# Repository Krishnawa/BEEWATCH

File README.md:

## Cloning the Repository and Updating Submodules  

To properly set up this project, follow these steps:  

### 1. Clone the Repository  
Use the `--recurse-submodules` flag to clone the repository along with its submodules:  

```sh
git clone --recurse-submodules https://github.com/Krishnawa/BEEWATCH.git
```
If you have already cloned the repository without submodules, initialize and update them manually:
```sh
git submodule update --init --recursive --remote
```

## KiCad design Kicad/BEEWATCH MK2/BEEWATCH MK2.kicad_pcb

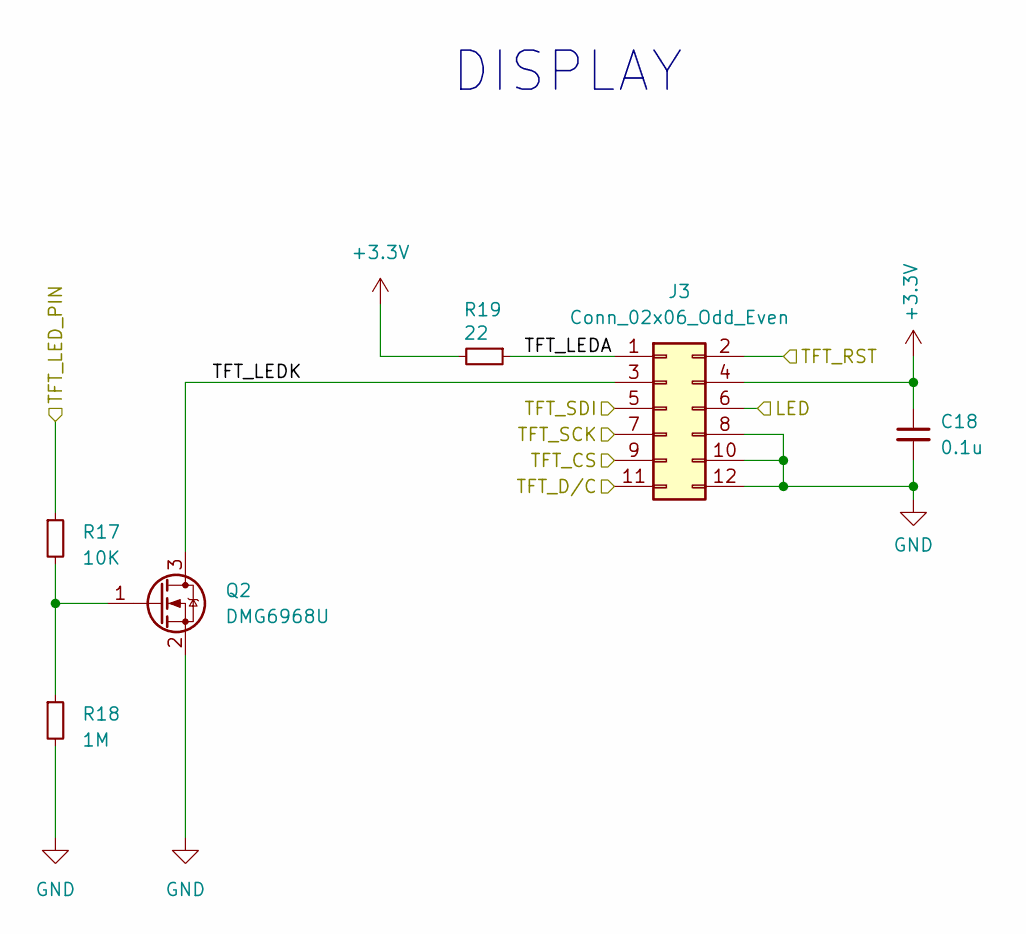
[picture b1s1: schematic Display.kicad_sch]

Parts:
C18: 0.1u; C_0603_1608Metric
J3: Conn_02x06_Odd_Even; PinHeader_2x06_P1.27mm_Vertical_SMD
Q2: DMG6968U; SOT-23
R17: 10K; R_0402_1005Metric_Pad0.72x0.64mm_HandSolder
R18: 1M; R_0402_1005Metric_Pad0.72x0.64mm_HandSolder
R19: 22; R_0402_1005Metric_Pad0.72x0.64mm_HandSolder

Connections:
+3.3V: C18.1, J3.4, R19.2; also elsewhere on the board
/Display/LED: J3.6; also elsewhere on the board
/Display/TFT_CS: J3.9; also elsewhere on the board
/Display/TFT_D/C: J3.11; also elsewhere on the board
/Display/TFT_LEDA: J3.1, R19.1
/Display/TFT_LEDK: J3.3, Q2.3 (D)
/Display/TFT_LED_PIN: R17.1; also elsewhere on the board
/Display/TFT_RST: J3.2; also elsewhere on the board
/Display/TFT_SCK: J3.7; also elsewhere on the board
/Display/TFT_SDI: J3.5; also elsewhere on the board
GND: C18.2, J3.8, J3.10, J3.12, Q2.2 (S), R18.2; also elsewhere on the board
unnamed: Q2.1 (G), R17.2, R18.1

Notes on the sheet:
DISPLAY

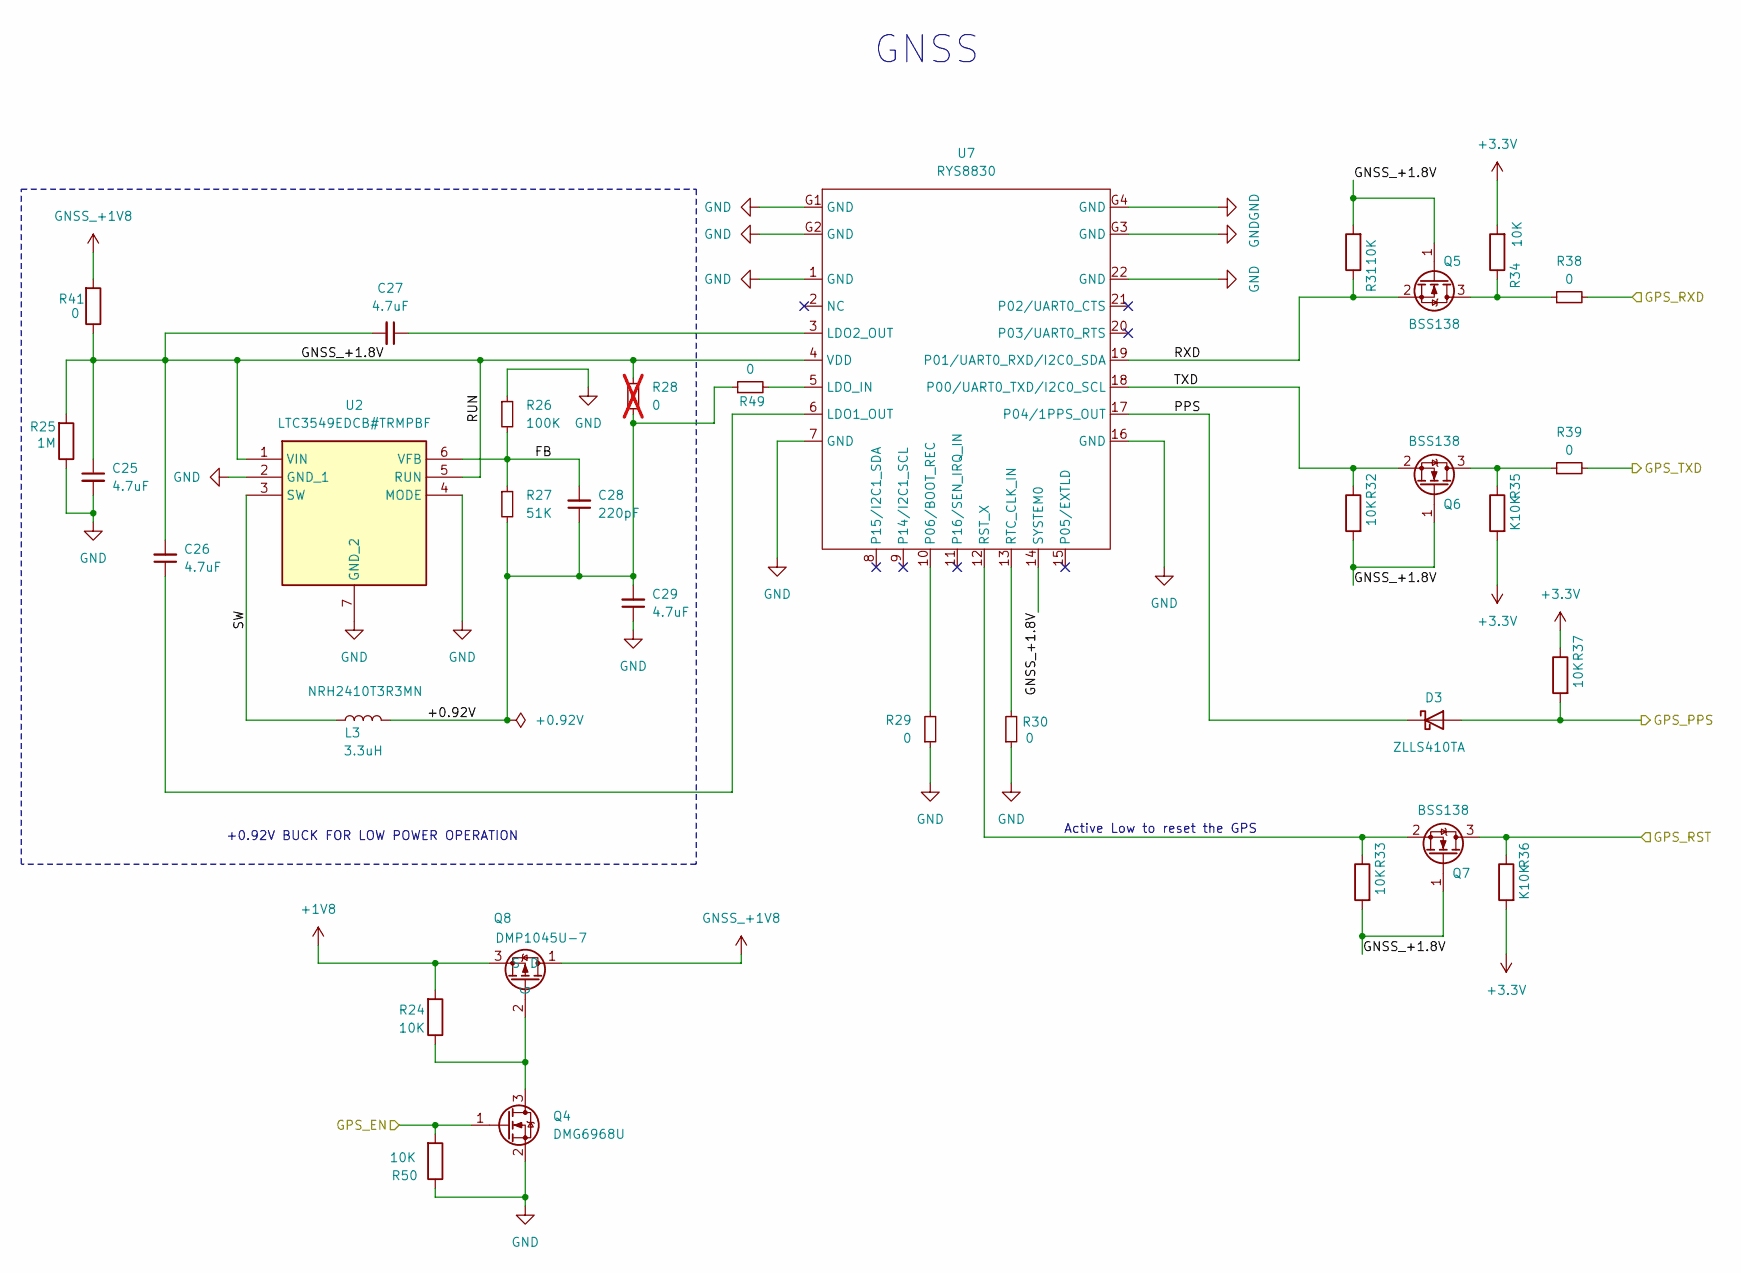
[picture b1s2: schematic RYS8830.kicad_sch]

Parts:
C25, C26, C27, C29: 4.7uF; C_0603_1608Metric
C28: 220pF; C_0603_1608Metric
D3: ZLLS410TA; D_SOD-323F
L3: 3.3uH; L_Cenker_CKCS3012; MPN NRH2410T3R3MN
Q4: DMG6968U; SOT-23
Q5, Q6, Q7: BSS138; SOT-23
Q8: DMP1045U-7; SOT-23-3
R24, R31, R32, R33, R34, R37, R50: 10K; R_0402_1005Metric_Pad0.72x0.64mm_HandSolder
R25: 1M; R_0402_1005Metric_Pad0.72x0.64mm_HandSolder
R26: 100K; R_0402_1005Metric_Pad0.72x0.64mm_HandSolder
R27: 51K; R_0402_1005Metric_Pad0.72x0.64mm_HandSolder
R28: 0; R_0402_1005Metric_Pad0.72x0.64mm_HandSolder; not fitted
R29, R30, R38, R39, R41, R49: 0; R_0402_1005Metric_Pad0.72x0.64mm_HandSolder
R35, R36: K10K; R_0402_1005Metric_Pad0.72x0.64mm_HandSolder
U2: LTC3549EDCB#TRMPBF; SON50P300X200X80-7N-D
U7: RYS8830

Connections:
+1V8: Q8.3 (S), R24.2; also elsewhere on the board
+3.3V: R34.2, R35.2, R36.2, R37.1; also elsewhere on the board
/ESP32/GPS_EN: Q4.1 (G), R50.2; also elsewhere on the board
/ESP32/GPS_PSS: D3.2 (A), R37.2; also elsewhere on the board
/ESP32/GPS_RST: Q7.3 (D), R36.1; also elsewhere on the board
/ESP32/GPS_RXD: R39.2; also elsewhere on the board
/ESP32/GPS_TXD: R38.2; also elsewhere on the board
/RYS8830/+0.92V: C28.1, C29.2, L3.2, R27.2, R28.2, R49.1
/RYS8830/FB: C28.2, R26.2, R27.1, U2.6 (VFB)
/RYS8830/GNSS_+1.8V: C25.1, C26.2, C27.2, Q5.1 (G), Q6.1 (G), Q7.1 (G), R25.2, R28.1, R31.2, R32.2, R33.2, R41.1, U2.1 (VIN), U2.5 (RUN), U7.4 (VDD), U7.14 (SYSTEM0)
/RYS8830/PPS: D3.1 (K), U7.17 (P04/1PPS_OUT)
/RYS8830/RXD: Q5.2 (S), R31.1, U7.19 (P01/UART0_RXD/I2C0_SDA)
/RYS8830/SW: L3.1, U2.3 (SW)
/RYS8830/TXD: Q6.2 (S), R32.1, U7.18 (P00/UART0_TXD/I2C0_SCL)
GND: C25.2, C29.1, Q4.2 (S), R25.1, R26.1, R29.1, R30.1, R50.1, U2.2 (GND_1), U2.4 (MODE), U2.7 (GND_2), U7.1 (GND), U7.7 (GND), U7.16 (GND), U7.22 (GND), U7.G1 (GND), U7.G2 (GND), U7.G3 (GND), U7.G4 (GND); also elsewhere on the board
GNSS_+1V8: Q8.1 (D), R41.2
unnamed: Q4.3 (D), Q8.2 (G), R24.1
unnamed: Q5.3 (D), R34.1, R38.1
unnamed: Q6.3 (D), R35.1, R39.1
unnamed: Q7.2 (S), R33.1, U7.12 (RST_X)
unnamed: C26.1, U7.6 (LDO1_OUT)
unnamed: C27.1, U7.3 (LDO2_OUT)
unnamed: R49.2, U7.5 (LDO_IN)
unnamed: R29.2, U7.10 (P06/BOOT_REC)
unnamed: R30.2, U7.13 (RTC_CLK_IN)

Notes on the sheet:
GNSS
Active Low to reset the GPS
+0.92V BUCK FOR LOW POWER OPERATION

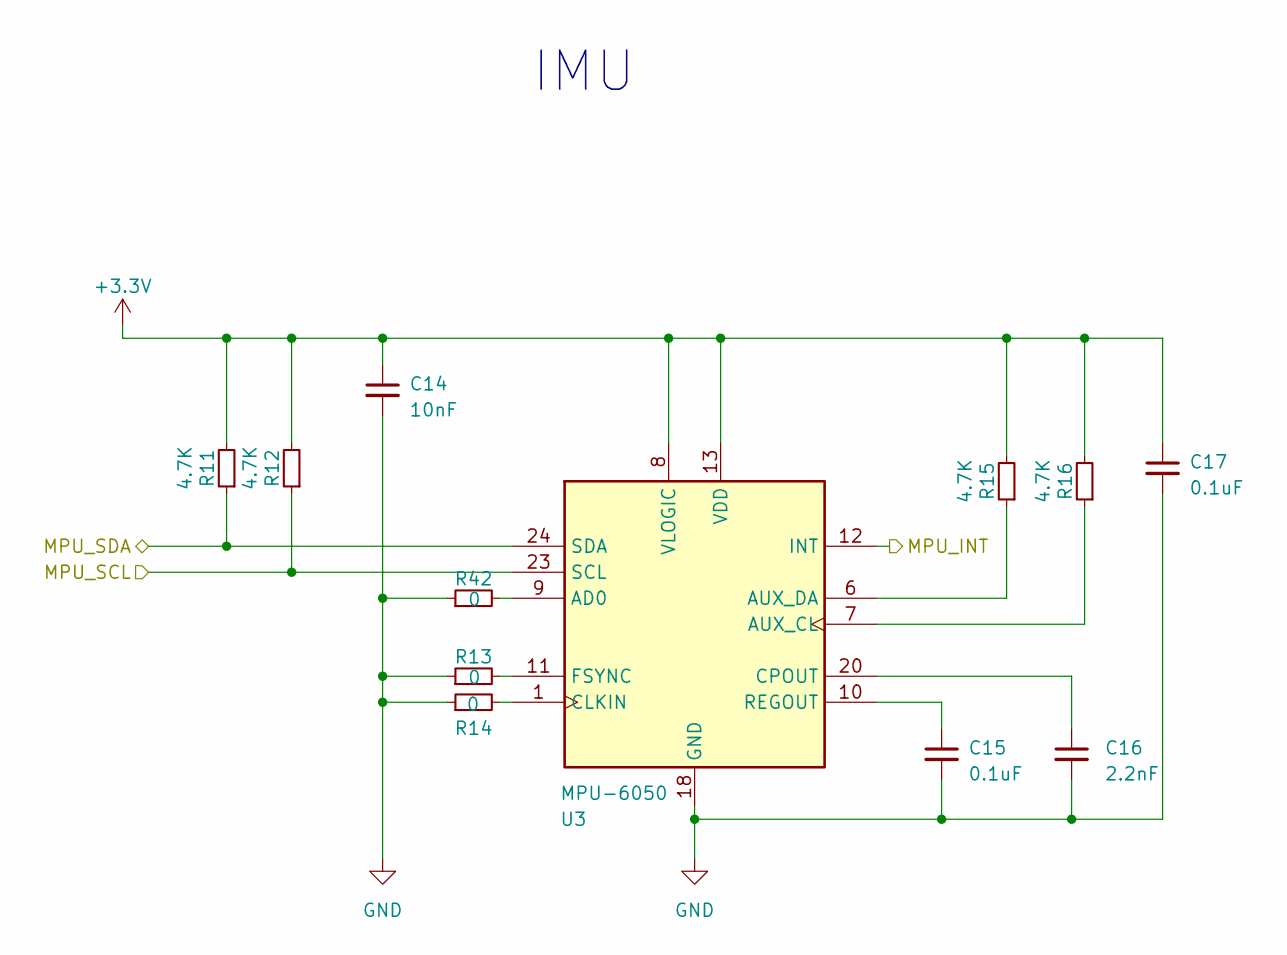
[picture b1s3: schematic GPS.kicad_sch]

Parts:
C14: 10nF; C_0603_1608Metric
C15, C17: 0.1uF; C_0603_1608Metric
C16: 2.2nF; C_0603_1608Metric
R11, R12, R15, R16: 4.7K; R_0402_1005Metric_Pad0.72x0.64mm_HandSolder
R13, R14, R42: 0; R_0402_1005Metric_Pad0.72x0.64mm_HandSolder
U3: MPU-6050; InvenSense_QFN-24_4x4mm_P0.5mm

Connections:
+3.3V: C14.1, C17.1, R11.2, R12.2, R15.2, R16.2, U3.8 (VLOGIC), U3.13 (VDD); also elsewhere on the board
/ACCELEROMETER/MPU_INT: U3.12 (INT); also elsewhere on the board
/ACCELEROMETER/MPU_SCL: R12.1, U3.23 (SCL); also elsewhere on the board
/ACCELEROMETER/MPU_SDA: R11.1, U3.24 (SDA); also elsewhere on the board
GND: C14.2, C15.2, C16.2, C17.2, R13.1, R14.1, R42.1, U3.18 (GND); also elsewhere on the board
unnamed: R42.2, U3.9 (AD0)
unnamed: R16.1, U3.7 (AUX_CL)
unnamed: R15.1, U3.6 (AUX_DA)
unnamed: R14.2, U3.1 (CLKIN)
unnamed: C16.1, U3.20 (CPOUT)
unnamed: R13.2, U3.11 (FSYNC)
unnamed: C15.1, U3.10 (REGOUT)

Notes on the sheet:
IMU

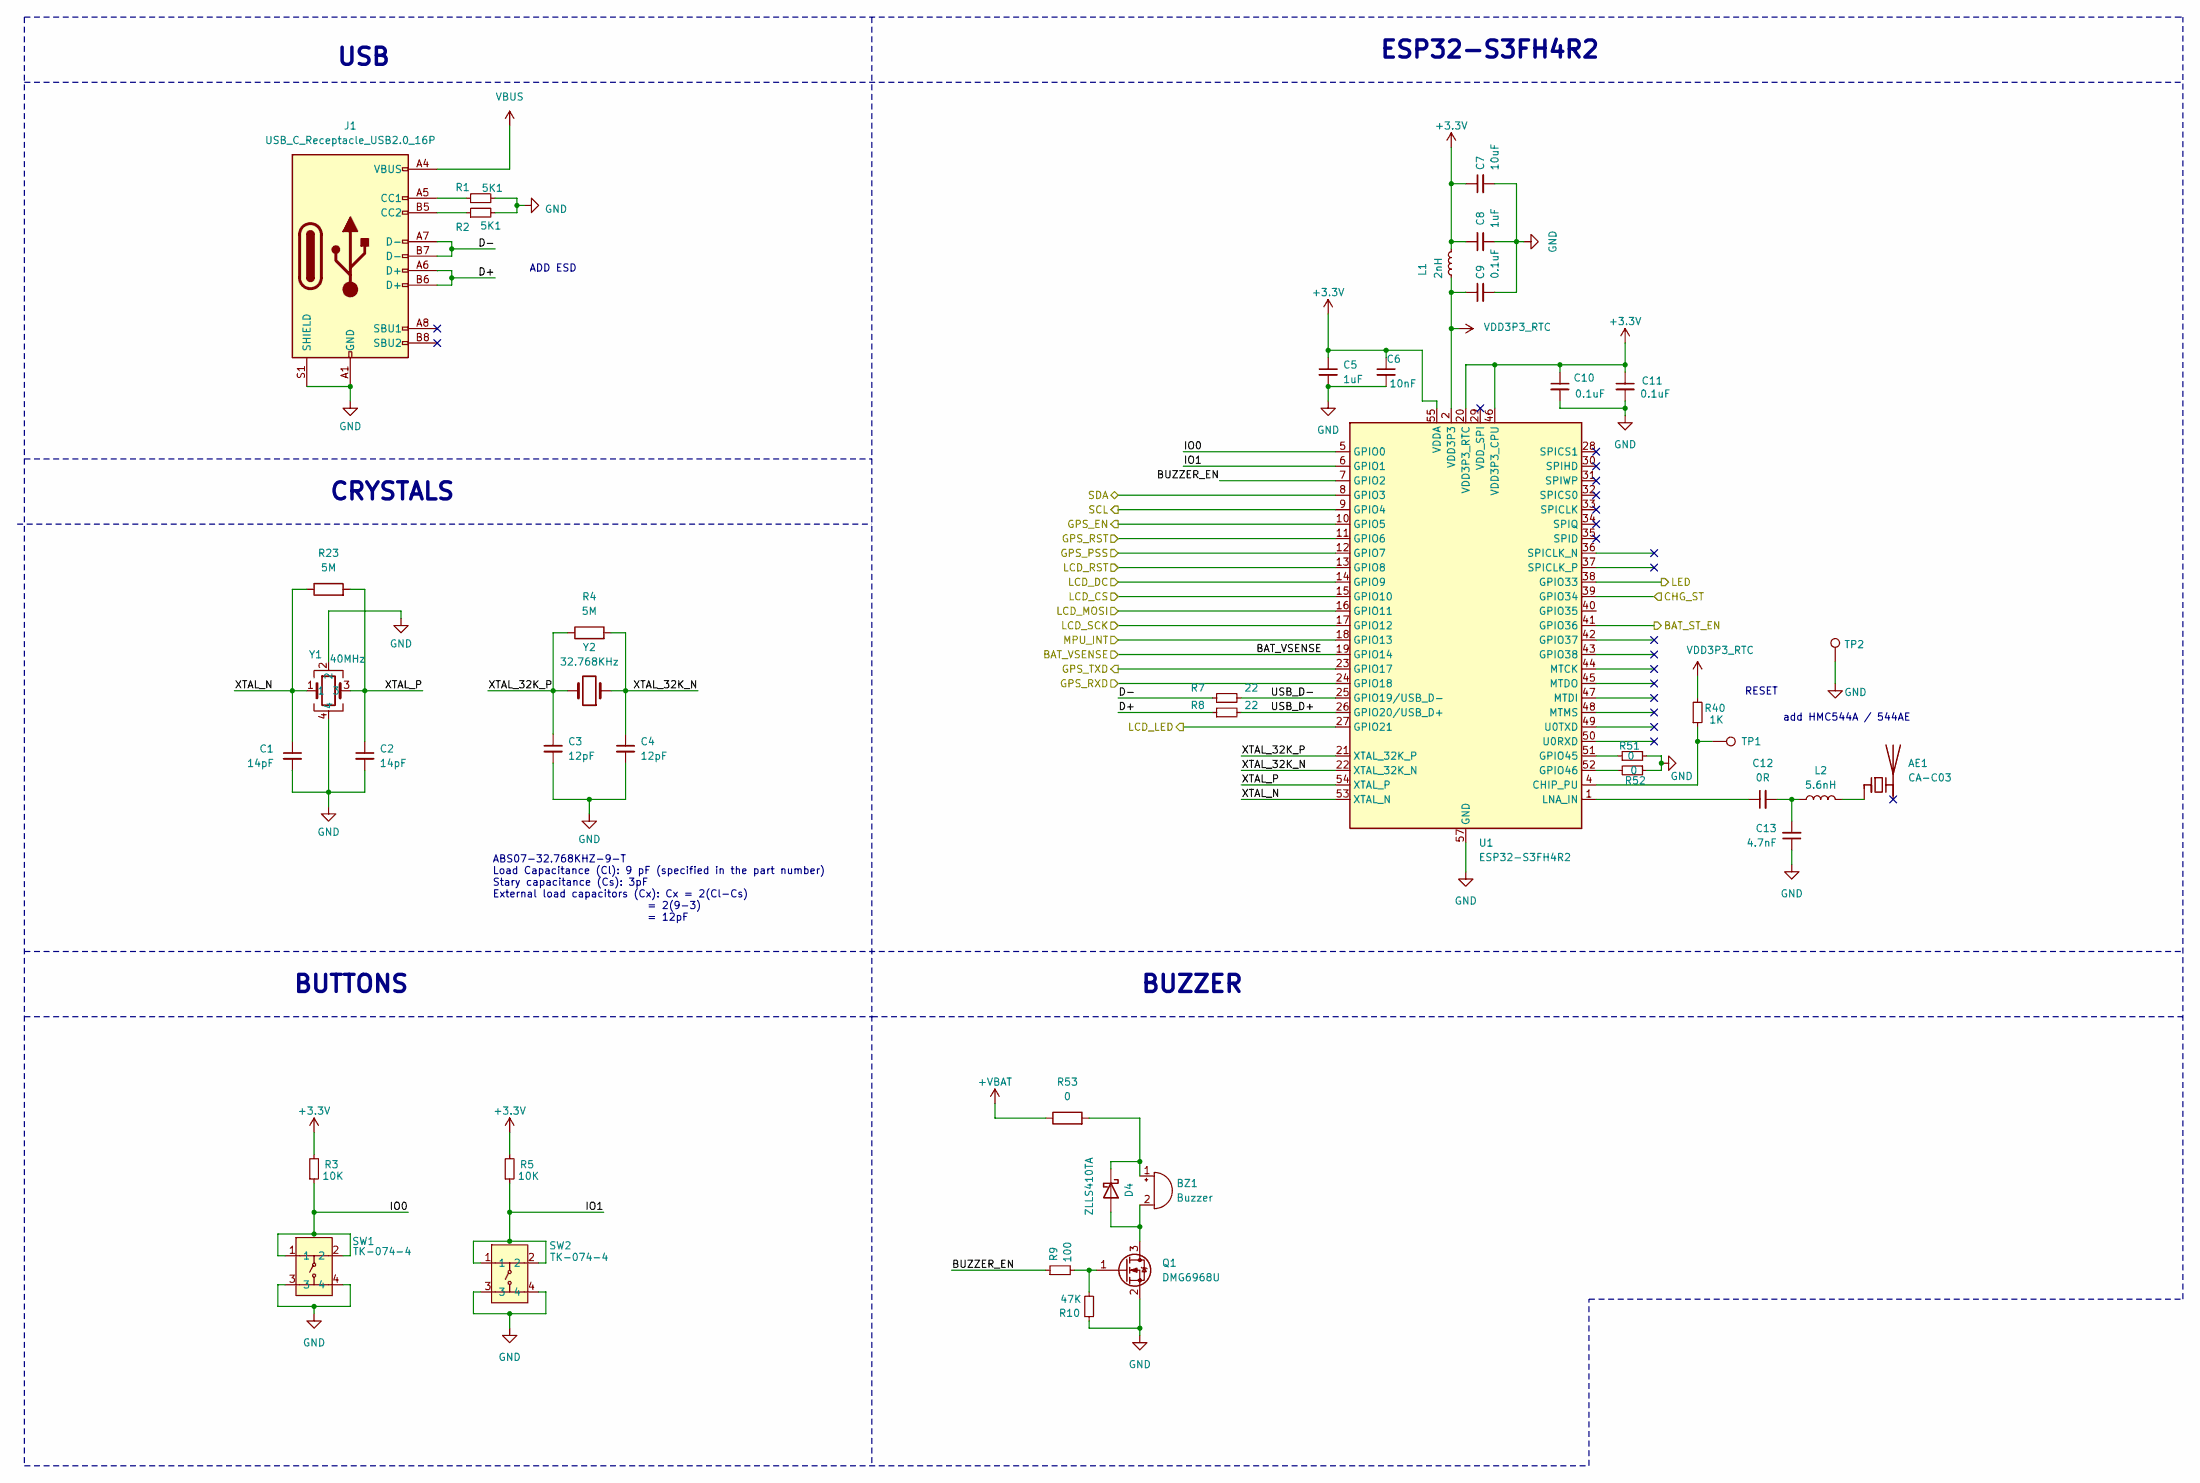
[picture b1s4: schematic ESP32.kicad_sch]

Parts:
AE1: CA-C03; ESP32_ZERO_ANT
BZ1: Buzzer; CL9032A-CLDZ-SMD Passive Buzzer
C1, C2: 14pF; C_0201_0603Metric
C3, C4: 12pF; C_0201_0603Metric
C5, C8: 1uF; C_0402_1005Metric_Pad0.74x0.62mm_HandSolder
C6: 10nF; C_0402_1005Metric_Pad0.74x0.62mm_HandSolder
C7: 10uF; C_0402_1005Metric_Pad0.74x0.62mm_HandSolder
C9, C10, C11: 0.1uF; C_0402_1005Metric_Pad0.74x0.62mm_HandSolder
C12: 0R; C_0402_1005Metric_Pad0.74x0.62mm_HandSolder
C13: 4.7nF; C_0402_1005Metric_Pad0.74x0.62mm_HandSolder
D4: ZLLS410TA; D_SOD-323F
J1: USB_C_Receptacle_USB2.0_16P; USB_C_Receptacle_XKB_U262-16XN-4BVC11
L1: 2nH; L_0402_1005Metric
L2: 5.6nH; L_0402_1005Metric
Q1: DMG6968U; SOT-23
R1, R2: 5K1; R_0402_1005Metric_Pad0.72x0.64mm_HandSolder
R3, R5: 10K; R_0402_1005Metric_Pad0.72x0.64mm_HandSolder
R4, R23: 5M; R_0402_1005Metric_Pad0.72x0.64mm_HandSolder
R7, R8: 22; R_0402_1005Metric_Pad0.72x0.64mm_HandSolder
R9: 100; R_0402_1005Metric_Pad0.72x0.64mm_HandSolder
R10: 47K; R_0402_1005Metric_Pad0.72x0.64mm_HandSolder
R40: 1K; R_0402_1005Metric_Pad0.72x0.64mm_HandSolder
R51, R52, R53: 0; R_0402_1005Metric_Pad0.72x0.64mm_HandSolder
SW1, SW2: TK-074-4; Tact Switch-TK-074-4 Pin SMD
TP1, TP2: TestPoint; TestPoint_Pad_D1.0mm
U1: ESP32-S3FH4R2; QFN-56-1EP_7x7mm_P0.4mm_EP4x4mm
Y1: 40MHz; Crystal_SMD_2016-4Pin_2.0x1.6mm
Y2: 32.768KHz; Crystal_SMD_EuroQuartz_EQ161-2Pin_3.2x1.5mm

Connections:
+3.3V: C5.1, C6.1, C7.1, C8.1, C10.1, C11.1, L1.2, R3.2, R5.2, U1.20 (VDD3P3_RTC), U1.46 (VDD3P3_CPU), U1.55 (VDDA), U1.56 (VDDA); also elsewhere on the board
+VBAT: R53.1; also elsewhere on the board
/ACCELEROMETER/MPU_INT: U1.18 (GPIO13); also elsewhere on the board
/ACCELEROMETER/MPU_SCL: U1.9 (GPIO4); also elsewhere on the board
/ACCELEROMETER/MPU_SDA: U1.8 (GPIO3); also elsewhere on the board
/Battery&BMS/BAT_SENSE_EN: U1.41 (GPIO36); also elsewhere on the board
/Battery&BMS/CHG_ST: U1.39 (GPIO34); also elsewhere on the board
/Display/LED: U1.38 (GPIO33); also elsewhere on the board
/Display/TFT_CS: U1.15 (GPIO10); also elsewhere on the board
/Display/TFT_D/C: U1.14 (GPIO9); also elsewhere on the board
/Display/TFT_LED_PIN: U1.27 (GPIO21); also elsewhere on the board
/Display/TFT_RST: U1.13 (GPIO8); also elsewhere on the board
/Display/TFT_SCK: U1.17 (GPIO12); also elsewhere on the board
/Display/TFT_SDI: U1.16 (GPIO11); also elsewhere on the board
/ESP32/BAT_VSENSE: U1.19 (GPIO14); also elsewhere on the board
/ESP32/BUZZER_EN: R9.1, U1.7 (GPIO2)
/ESP32/D+: J1.A6 (D+), J1.B6 (D+), R8.1
/ESP32/D-: J1.A7 (D-), J1.B7 (D-), R7.1
/ESP32/GPS_EN: U1.10 (GPIO5); also elsewhere on the board
/ESP32/GPS_PSS: U1.12 (GPIO7); also elsewhere on the board
/ESP32/GPS_RST: U1.11 (GPIO6); also elsewhere on the board
/ESP32/GPS_RXD: U1.24 (GPIO18); also elsewhere on the board
/ESP32/GPS_TXD: U1.23 (GPIO17); also elsewhere on the board
/ESP32/IO0: R3.1, SW1.1, SW1.2, U1.5 (GPIO0)
/ESP32/IO1: R5.1, SW2.1, SW2.2, U1.6 (GPIO1)
/ESP32/USB_D+: R8.2, U1.26 (GPIO20/USB_D+)
/ESP32/USB_D-: R7.2, U1.25 (GPIO19/USB_D-)
/ESP32/XTAL_32K_N: C4.1, R4.2, U1.22 (XTAL_32K_N), Y2.1
/ESP32/XTAL_32K_P: C3.1, R4.1, U1.21 (XTAL_32K_P), Y2.2
/ESP32/XTAL_N: C1.1, R23.1, U1.53 (XTAL_N), Y1.1
/ESP32/XTAL_P: C2.1, R23.2, U1.54 (XTAL_P), Y1.3
GND: C1.2, C2.2, C3.2, C4.2, C5.2, C6.2, C7.2, C8.2, C9.2, C10.2, C11.2, C13.1, J1.A1 (GND), J1.A12 (GND), J1.B1 (GND), J1.B12 (GND), J1.S1 (SHIELD), Q1.2 (S), R1.2, R2.2, R10.1, R51.2, R52.1, SW1.3, SW1.4, SW2.3, SW2.4, TP2.1, U1.57 (GND), Y1.2, Y1.4; also elsewhere on the board
unnamed: AE1.1 (FEED), L2.2
unnamed: BZ1.1 (+), D4.1 (K), R53.2
unnamed: BZ1.2 (-), D4.2 (A), Q1.3 (D)
unnamed: C12.2, C13.2, L2.1
unnamed: J1.A5 (CC1), R1.1
unnamed: J1.B5 (CC2), R2.1
unnamed: Q1.1 (G), R9.2, R10.2
unnamed: R40.1, TP1.1, U1.4 (CHIP_PU)
unnamed: R51.1, U1.51 (GPIO45)
unnamed: R52.2, U1.52 (GPIO46)
unnamed: C12.1, U1.1 (LNA_IN)
VBUS: J1.A4 (VBUS), J1.A9 (VBUS), J1.B4 (VBUS), J1.B9 (VBUS); also elsewhere on the board
VDD3P3_RTC: C9.1, L1.1, R40.2, U1.2 (VDD3P3), U1.3 (VDD3P3)

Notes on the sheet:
BUZZER
USB
CRYSTALS
BUTTONS
RESET
ESP32-S3FH4R2
add HMC544A / 544AE
ABS07-32.768KHZ-9-T Load Capacitance (Cl): 9 pF (specified in the part number) Stary capacitance (Cs): 3pF External load capacitors (Cx): Cx = 2(Cl-Cs) = 2(9-3) = 12pF
ADD ESD

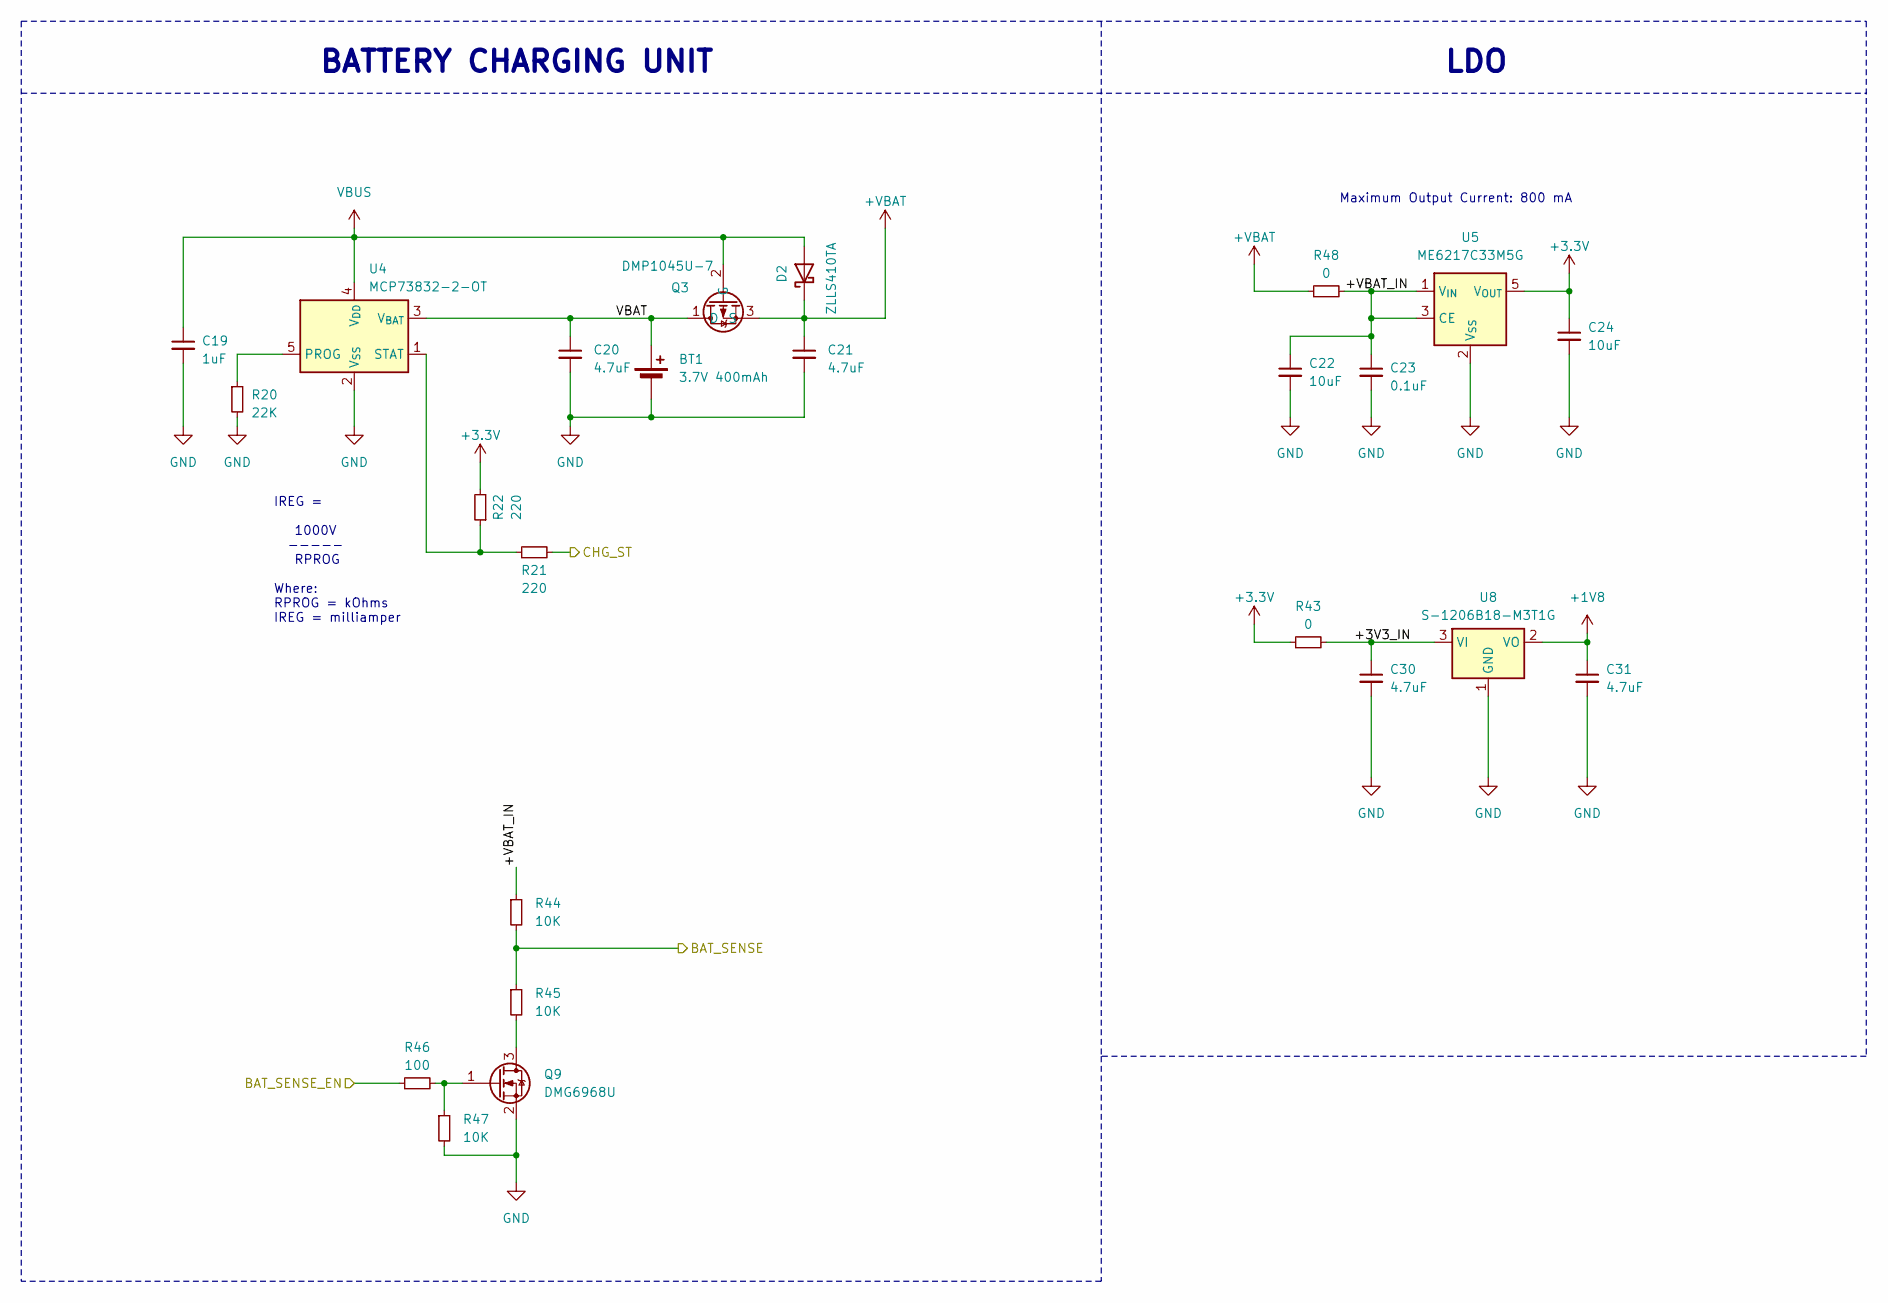
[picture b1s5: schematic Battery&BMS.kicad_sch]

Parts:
BT1: 3.7V 400mAh; WLY902025
C19: 1uF; C_0603_1608Metric
C20, C21, C30, C31: 4.7uF; C_0603_1608Metric
C22: 10uF; C_0402_1005Metric_Pad0.74x0.62mm_HandSolder
C23: 0.1uF; C_0402_1005Metric_Pad0.74x0.62mm_HandSolder
C24: 10uF; C_0603_1608Metric
D2: ZLLS410TA; D_SOD-323F
Q3: DMP1045U-7; SOT-23-3
Q9: DMG6968U; SOT-23
R20: 22K; R_0402_1005Metric_Pad0.72x0.64mm_HandSolder
R21, R22: 220; R_0402_1005Metric_Pad0.72x0.64mm_HandSolder
R43, R48: 0; R_0402_1005Metric_Pad0.72x0.64mm_HandSolder
R44, R45, R47: 10K; R_0402_1005Metric_Pad0.72x0.64mm_HandSolder
R46: 100; R_0402_1005Metric_Pad0.72x0.64mm_HandSolder
U4: MCP73832-2-OT; SOT-23-5
U5: ME6217C33M5G; SOT-23-5
U8: S-1206B18-M3T1G; SOT-23-3

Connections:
+1V8: C31.1, U8.2 (VO); also elsewhere on the board
+3.3V: C24.1, R22.2, R43.1, U5.5 (V_{OUT}); also elsewhere on the board
+VBAT: C21.1, D2.1 (K), Q3.3 (S), R48.1; also elsewhere on the board
/Battery&BMS/+3V3_IN: C30.1, R43.2, U8.3 (VI)
/Battery&BMS/+VBAT_IN: C22.1, C23.1, R44.1, R48.2, U5.1 (V_{IN}), U5.3 (CE)
/Battery&BMS/BAT_SENSE_EN: R46.1; also elsewhere on the board
/Battery&BMS/CHG_ST: R21.2; also elsewhere on the board
/Battery&BMS/VBAT: BT1.1 (+), C20.1, Q3.1 (D), U4.3 (V_{BAT})
/ESP32/BAT_VSENSE: R44.2, R45.1; also elsewhere on the board
GND: BT1.2 (-), C19.2, C20.2, C21.2, C22.2, C23.2, C24.2, C30.2, C31.2, Q9.2 (S), R20.2, R47.2, U4.2 (V_{SS}), U5.2 (V_{SS}), U8.1 (GND); also elsewhere on the board
unnamed: Q9.3 (D), R45.2
unnamed: Q9.1 (G), R46.2, R47.1
unnamed: R20.1, U4.5 (PROG)
unnamed: R21.1, R22.1, U4.1 (STAT)
VBUS: C19.1, D2.2 (A), Q3.2 (G), U4.4 (V_{DD}); also elsewhere on the board

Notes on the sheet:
Maximum Output Current: 800 mA
LDO
BATTERY CHARGING UNIT
IREG = 1000V ----- RPROG Where: RPROG = kOhms IREG = milliamper

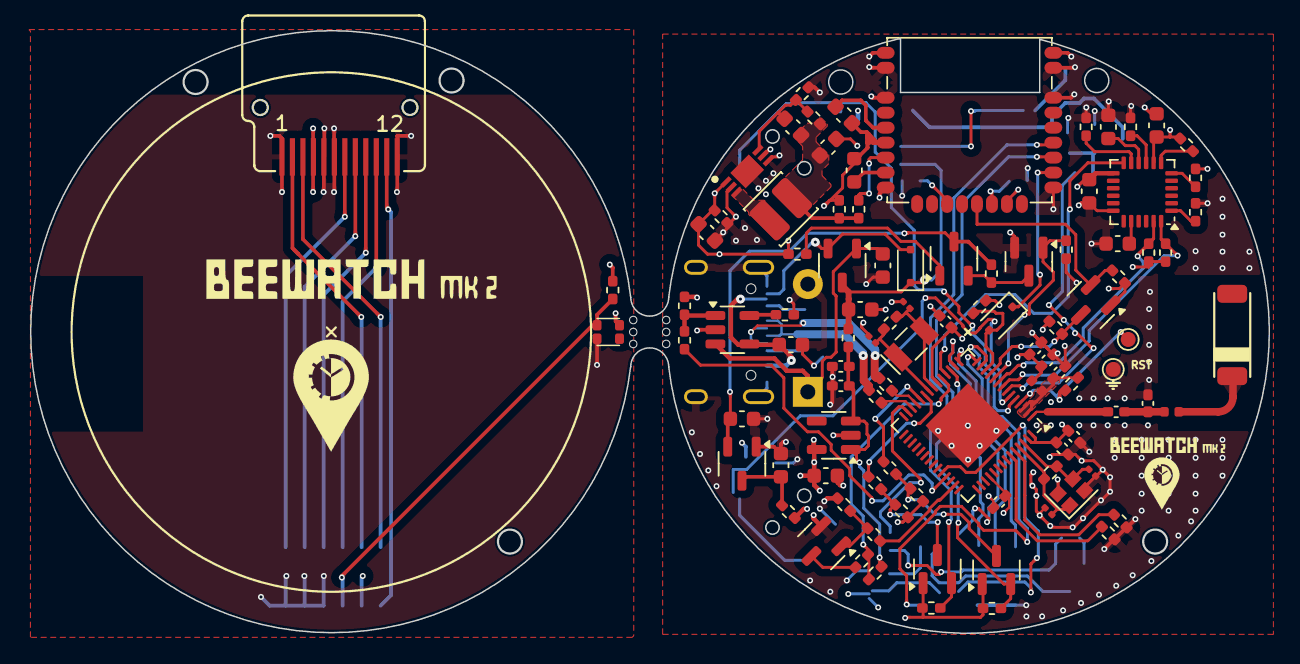
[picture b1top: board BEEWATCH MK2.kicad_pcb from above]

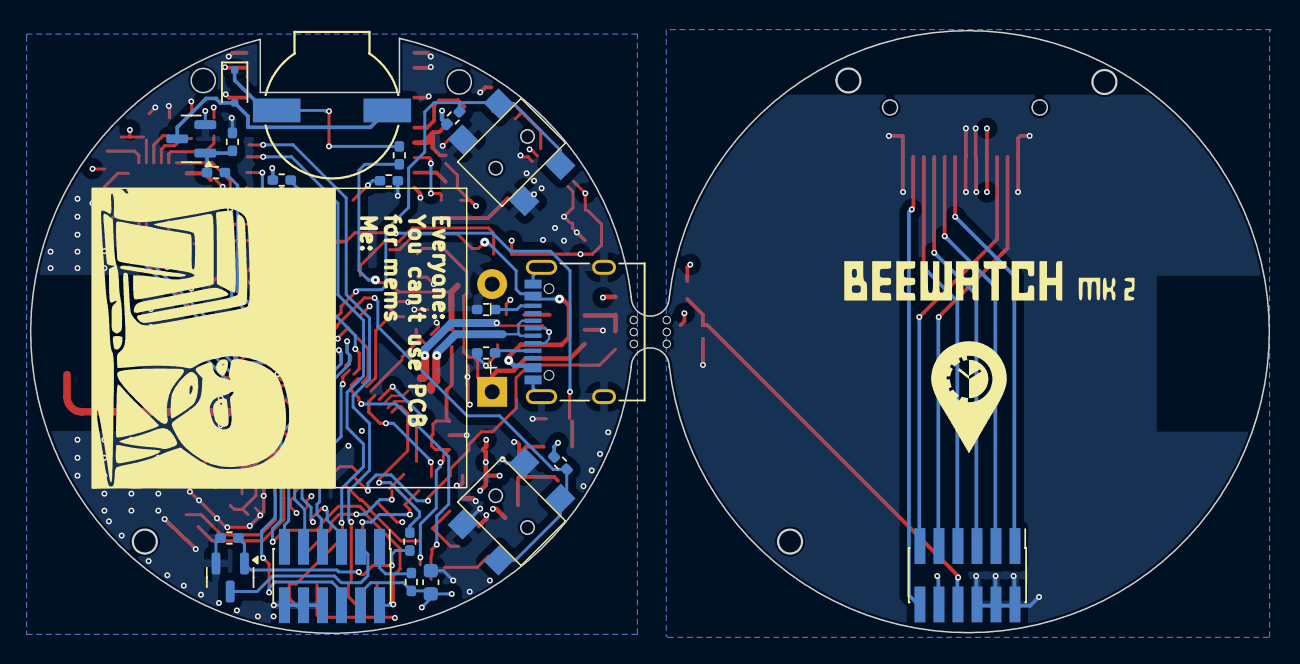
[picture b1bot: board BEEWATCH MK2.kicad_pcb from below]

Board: 4 copper layers, 82.7 x 40.2 mm, 122 parts (24 on the bottom side), 90 nets.

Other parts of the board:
D1: WS2812B-0807; XL-0807RGBC-WS2812B
DS1: GC9A01; GC9A01_BOTTOM
J4: Conn_02x06_Odd_Even; PinHeader_2x06_P1.27mm_Vertical_SMD
R6: 1K; R_0402_1005Metric_Pad0.72x0.64mm_HandSolder
meme_2: LOGO; meme_2
mouse-bite-2.54mm-slot: VAL**; mouse-bite-2.54mm-slot

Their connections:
/Display board/3V3: D1.1 (VDD), DS1.4 (VDD), J4.10, R6.2
/Display board/CS: DS1.8 (~CS), J4.3
/Display board/D/C: DS1.7 (D/C), J4.1
/Display board/LED_A: DS1.3 (LEDA), J4.11
/Display board/LED_K: DS1.2 (LEDK), J4.9
/Display board/RST: DS1.11 (~RESET), J4.12
/Display board/SCK: DS1.9 (SCK), J4.5
/Display board/SDI: DS1.10 (SDI), J4.7
/Display board/_GND: D1.3 (VSS), DS1.1 (GND), DS1.5 (GND), DS1.6 (GND), DS1.12 (GND), J4.2, J4.4, J4.6
/Display board/_LED: D1.2 (DOUT), J4.8, R6.1

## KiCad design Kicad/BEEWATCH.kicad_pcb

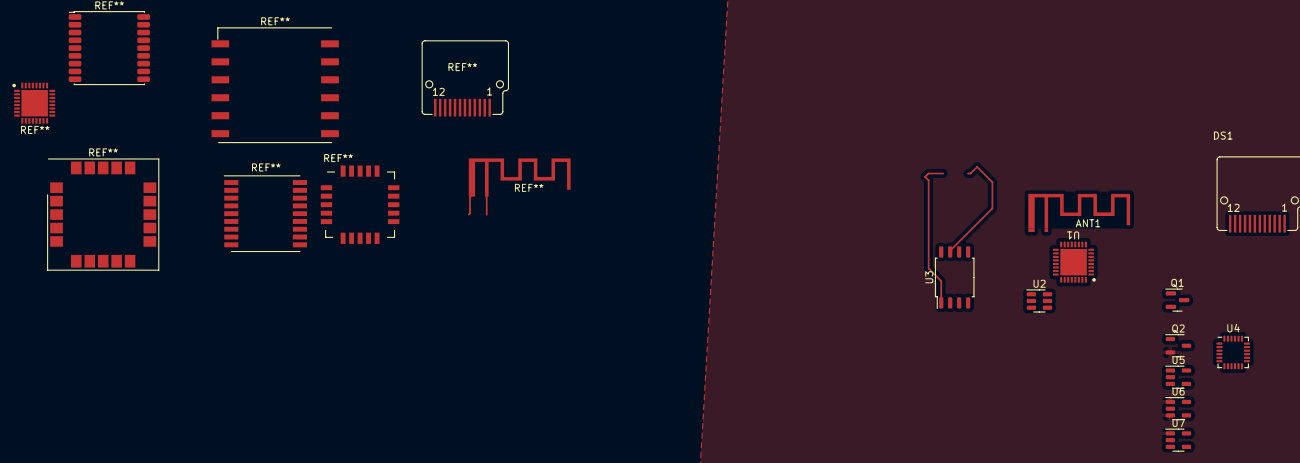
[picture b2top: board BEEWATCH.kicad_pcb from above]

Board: 2 copper layers, 11 parts (0 on the bottom side), 16 nets.

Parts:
ANT1: IFA_2.4GHz
DS1: GC9A01_TOP
Q1: 2N7002; SOT-23
Q2: SOT-23-3
U1: ESP32-C3; VFQFN-32
U2: USBLC6-2SC6; SOT-23-6
U3: W25Q128JVS; SOIC-8_5.23x5.23mm_P1.27mm
U4: MPU-6050; InvenSense_QFN-24_4x4mm_P0.5mm
U5: MCP73832-2-OT; SOT-23-5
U6, U7: XC6210B332MR; SOT-23-5

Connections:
+3.3V: U1.11 (VDD3P3_RTC), U1.17 (VDD3P3_CPU), U1.31 (VDDA), U1.32 (VDDA), U2.5 (VBUS), U6.5 (VOUT)
+5V: Q2.2 (S), U6.1 (VIN), U6.3 (CE), U7.1 (VIN)
/ACCELEROMETER/3V3: U4.8 (VLOGIC), U4.13 (VDD)
/Battery&BMS/VBAT: Q2.3 (D), U5.3 (V_{BAT})
/Display/TFT_LEDK: DS1.2 (LEDK), Q1.3 (D)
/ESP32/DM-: U1.26 (GPIO19), U2.3 (I/O2)
/ESP32/DP+: U1.25 (GPIO18), U2.1 (I/O1)
/ESP32/SPI2_CLK: U1.12 (MTCK), U3.6 (CLK)
/ESP32/SPI2_CS0: U1.16 (GPIO10), U3.1 (~CS)
/ESP32/SPI2_MISO: U1.6 (GPIO2), U3.5 (DI(IO0))
/ESP32/SPI2_MOSI: U1.13 (MTDO), U3.2 (DO(IO1))
/ESP32/SPI2_QUADHD: U1.9 (MTMS), U3.7 (IO3)
/ESP32/SPI2_QUADWP: U1.10 (MTDI), U3.3 (IO2)
GND: ANT1.1 (GND), DS1.1 (GND), DS1.5 (GND), DS1.6 (GND), DS1.12 (GND), Q1.2 (S), U1.33 (EP), U2.2 (GND), U3.4 (GND), U4.9 (AD0), U4.18 (GND), U5.2 (V_{SS}), U6.2 (GND), U7.2 (GND)
unnamed: U1.2 (VDD3P3), U1.3 (VDD3P3)
VBUS: Q2.1 (G), U5.4 (V_{DD})

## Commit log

2023-03-09 working on schematics
2023-03-09 Inverted F Antenna designed
2023-03-09 Minor edits in IFA
2023-03-09 Created README.md
2023-03-10 GPS Removed
    GPS is expensive and difficult to find small factor foot print. So No GPS function
2023-03-10 GPS Removed
2023-03-13 Plan to add GPS
2023-03-13 Components selections
2023-03-13 Save Kicad files
2023-03-21 ESP32 Symbol minor edit
2023-03-21 Insufficient GPIOs planning to add/C MUX or MCU
2023-05-08 planning to shift to ESP32-D0WDQ6
2023-05-20 Added specification excel
2025-01-23 Kicad design is ongoing
2025-01-26 Rough layout placement
2025-01-26 Minor changes in the footprint lib
2025-01-26 Added QFN 3D files
2025-02-14 Update schema
2025-02-17 Schematic changes
2025-02-17 README changes
2025-02-18 GNSS level shifter floating voltage needs to be fix
2025-02-19 Added Buzzer flyback diode
2025-02-19 Added gitignore
2025-02-19 Replacing with submodule Lib
2025-02-19 Updated with sub module lib
2025-02-19 Added details of cloning in README
2025-02-20 Lib Integration almost done
2025-02-20 minor change in ESP32
2025-02-20 minor changes
2025-02-20 NAME changes
2025-02-24 Updated to KiCad 9!
2025-02-27 ERC Checking
2025-02-27 submodule update
2025-02-27 Addd Buck
2025-02-27 ERC going on anf All Lib issue is fixed
2025-02-28 Pending task Crystal footprint
2025-03-03 Crystal footprint fixed
2025-03-03 Deep optmizing the Layout
2025-03-04 Deep optmization 80% completed
2025-03-04 Deep optmization 90% completed
2025-03-05 Changed +3V3 to +3.3V
2025-03-05 Save project
2025-03-05 Deep optimization 100%
2025-03-06 Duplicate pin changed
2025-03-06 Routing ongoing
2025-03-11 Layout ongoing
2025-03-13 Layout almost completed
2025-03-13 Added Display lib
2025-03-13 Added display board schema
2025-03-13 Somehow finished the layout, but deep optimization required
2025-03-20 Added SMA connector
2025-03-20 Layout Finished but deep otimization required
2025-03-26 Removed SMA
2025-03-26 Need to update some values
2025-03-26 Project update
2025-03-26 Need to check thisI hope it's an extension
2025-04-12 Layout DRC ongoing
2025-04-12 Added net class colour
2025-04-12 Antenna layout completed
2025-04-12 Updated Antenna footprint
2025-04-13 Antenna and Schematic correction
2025-04-13 Updated submodule KiCadoodle to latest commit
2025-04-13 Hope this by next week gerbers will generate
2025-04-13 Display holes added
2025-04-20 Added Logo folder
2025-04-20 Added Buzzer datasheet
2025-04-20 Updated Library
2025-04-22 Added Panalized board file
2025-04-22 Updating MPN
2025-04-23 PCB Updated
2025-04-26 Added Rendered Photos
2025-04-26 Added Fab doc
2025-04-26 Added board2pdf config file
2025-04-26 Modified Assembly file
2025-04-26 Project updated
2025-04-30 PCB update
2025-05-07 Refining
2025-05-08 Changing to FAB capability
2025-05-14 Updated render photos
2025-05-14 Updated PCB file
2025-05-14 Updated Plots folder
2025-05-14 Removed old files
2025-08-31 Hide MPN
2025-12-04 Kicadoodle update......
